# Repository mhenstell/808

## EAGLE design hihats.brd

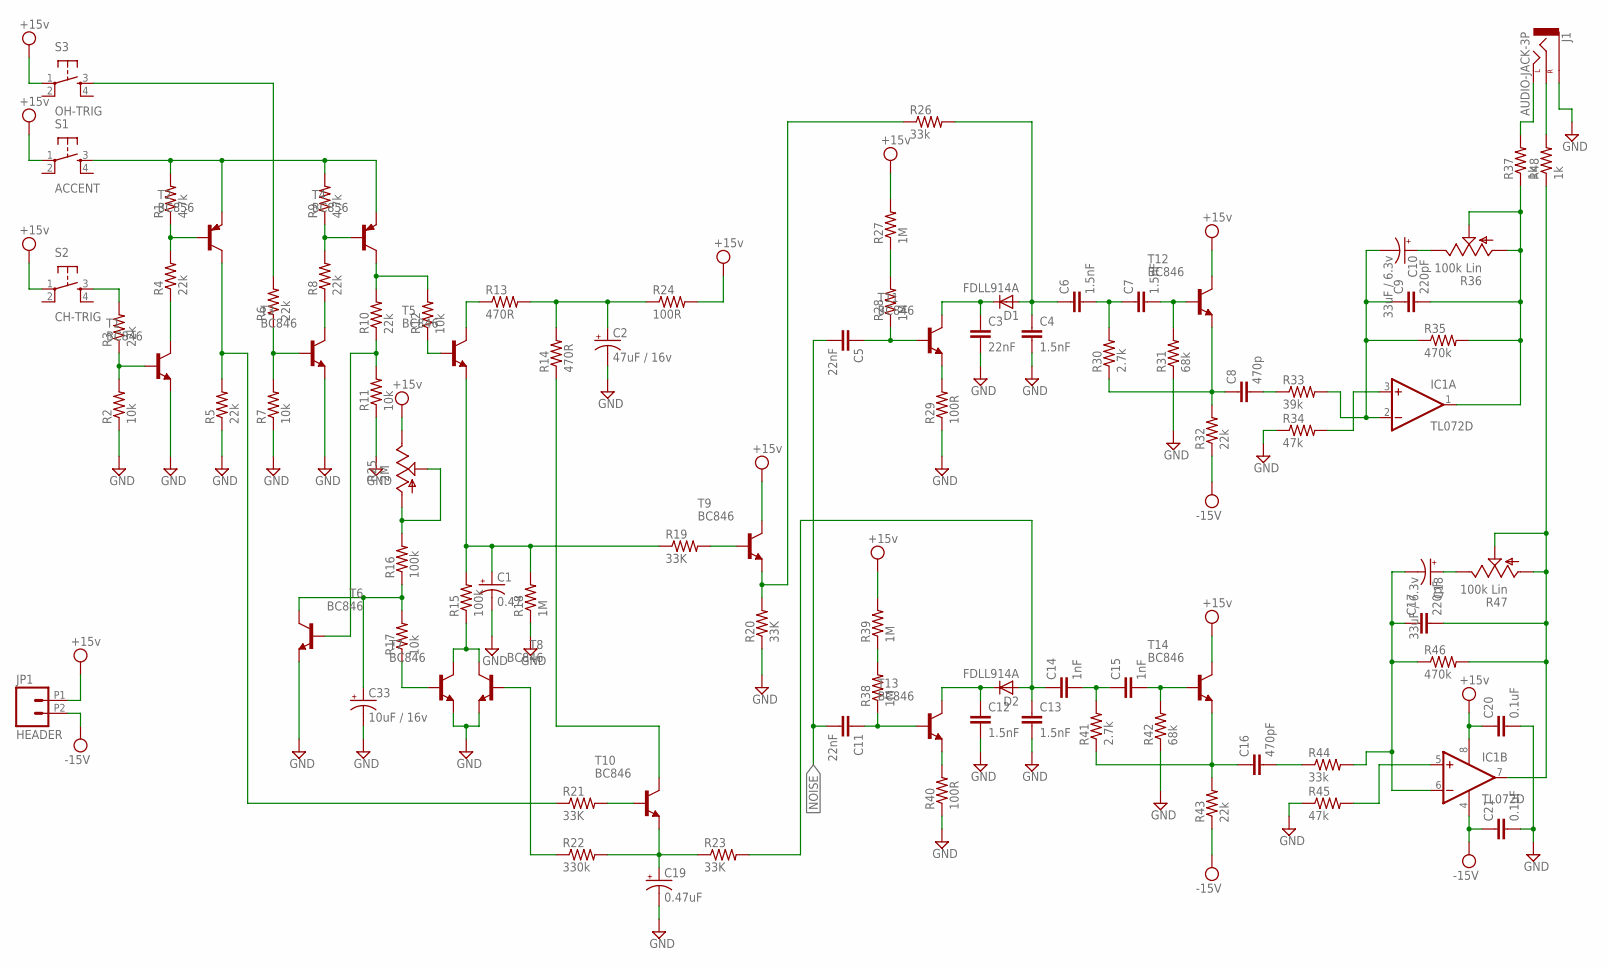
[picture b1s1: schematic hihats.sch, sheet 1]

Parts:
C1: 0.47; PANASONIC_VS_B-2; PARTNO EEE-1HAR47AR
C2: 47uF / 16v; PANASONIC_VS_B-2; PARTNO EEE-1CA470WR
C3, C5, C11: 22nF; 0805; PARTNO C0805C682K5RACTU
C4, C6, C7, C12, C13: 1.5nF; 0805; PARTNO C0805C682K5RACTU
C8: 470p; 0805; PARTNO C0805C682K5RACTU
C9, C17: 220pF; 0805; PARTNO C0805C682K5RACTU
C10, C18: 33uF / 6.3v; PANASONIC_VS_B-2; PARTNO EEE-1AA330WAR
C14, C15: 1nF; 0805; PARTNO C0805C682K5RACTU
C16: 470pF; 0805; PARTNO C0805C682K5RACTU
C19: 0.47uF; PANASONIC_VS_B-2; PARTNO UWJ1HR47MCL1GB
C20, C21: 0.1uF; 0805; PARTNO C0805C682K5RACTU
C33: 10uF / 16v; PANASONIC_VS_B-2; PARTNO EEE-1VA100WAR
D1, D2: FDLL914A; MELF-MLL34; PARTNO FDLL914A
IC1: TL072D; SO08; PARTNO TL072SG-13
J1: AUDIO-JACK-3P; CUI-352X-SMT; PARTNO SJ-3523-SMT-TR
JP1: HEADER; 1X02-5.08-SCREWTERM
R1, R9: 4.7k; 0805; PARTNO RMCF0805FT10K0
R2, R7, R11, R12, R17: 10k; 0805; PARTNO RMCF0805FT10K0
R3, R4, R5, R6, R8, R10, R32, R43: 22k; 0805; PARTNO RMCF0805FT10K0
R13, R14: 470R; 0805; PARTNO RMCF0805FT10K0
R15, R16: 100k; 0805; PARTNO RMCF0805FT10K0
R18, R27, R28, R38, R39: 1M; 0805; PARTNO RMCF0805FT10K0
R19, R20, R21, R23: 33K; 0805; PARTNO RMCF0805FT10K0
R22: 330k; 0805; PARTNO RMCF0805FT10K0
R24, R29, R40: 100R; 0805; PARTNO RMCF0805FT10K0
R25: 2M; POTENTIOMETER-3352P; PARTNO 3352P-1-205LF
R26, R44: 33k; 0805; PARTNO RMCF0805FT10K0
R30, R41: 2.7k; 0805; PARTNO RMCF0805FT10K0
R31, R42: 68k; 0805; PARTNO RMCF0805FT10K0
R33: 39k; 0805; PARTNO RMCF0805FT10K0
R34, R45: 47k; 0805; PARTNO RMCF0805FT10K0
R35, R46: 470k; 0805; PARTNO RMCF0805FT10K0
R36, R47: 100k Lin; POTENTIOMETER-CTS296; PARTNO 296UD104B1N
R37, R48: 1k; 0805; PARTNO RMCF0805FT10K0
S1: ACCENT; TACTILE_SWITCH_SMD; PARTNO PTS525SM10SMTR LFS
S2: CH-TRIG; TACTILE_SWITCH_SMD; PARTNO PTS525SM10SMTR LFS
S3: OH-TRIG; TACTILE_SWITCH_SMD; PARTNO PTS525SM10SMTR LFS
T1, T3, T5, T6, T7, T8, T9, T10, T11, T12, T13, T14: BC846; SOT23; PARTNO BC846BMTF
T2, T4: BC856; SOT23-BEC; PARTNO BC856BMTF

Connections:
+15V: C20.1, IC1.8 (V+), JP1.P1 (2), R24.2, R25.P$3 (E), R27.2, R39.2, S1.1, S2.1, S3.1, T9.3 (C), T12.3 (C), T14.3 (C); also elsewhere on the board
-15V: C21.1, IC1.4 (V-), JP1.P2 (1), R32.1, R43.1; also elsewhere on the board
GND: C1.-, C2.-, C3.2, C4.2, C12.2, C13.2, C19.-, C20.2, C21.2, C33.-, J1.1 (SLEEVE), R2.1, R5.1, R7.1, R11.1, R18.1, R20.1, R29.1, R31.1, R34.1, R40.1, R42.1, R45.1, T1.2 (E), T3.2 (E), T6.2 (E), T7.2 (E), T8.2 (E); also elsewhere on the board
unnamed: R1.2, R9.2, S1.3, T2.E, T4.E
unnamed: R1.1, R4.2, T2.B
unnamed: R3.2, S2.3
unnamed: R2.2, R3.1, T1.1 (B)
unnamed: R4.1, T1.3 (C)
unnamed: R8.2, R9.1, T4.B
unnamed: R5.2, R21.1, T2.C
unnamed: R6.2, S3.3
unnamed: R6.1, R7.2, T3.1 (B)
unnamed: R8.1, T3.3 (C)
unnamed: R10.2, R12.2, T4.C
unnamed: R10.1, R11.2, T6.1 (B)
unnamed: R12.1, T5.1 (B)
unnamed: R13.1, T5.3 (C)
unnamed: C2.+, R13.2, R14.2, R24.1
unnamed: R15.1, T7.3 (C), T8.3 (C)
unnamed: C33.+, R16.1, R17.2, T6.3 (C)
unnamed: R19.2, T9.1 (B)
unnamed: R17.1, T7.1 (B)
unnamed: R20.2, R26.1, T9.2 (E)
unnamed: R21.2, T10.1 (B)
unnamed: C1.+, R15.2, R18.2, R19.1, T5.2 (E)
unnamed: R22.1, T8.1 (B)
unnamed: C19.+, R22.2, R23.1, T10.2 (E)
unnamed: R14.1, T10.3 (C)
unnamed: C4.1, C6.1, D1.2 (A), R26.2
unnamed: R16.2, R25.P$1 (A), R25.P$2 (S)
unnamed: R27.1, R28.2
unnamed: C5.1, R28.1, T11.1 (B)
unnamed: R29.2, T11.2 (E)
unnamed: C3.1, D1.1 (C), T11.3 (C)
unnamed: C6.2, C7.1, R30.2
unnamed: C7.2, R31.2, T12.1 (B)
unnamed: C8.1, R30.1, R32.2, T12.2 (E)
unnamed: C8.2, R33.1
unnamed: C9.1, C10.-, IC1.2 (-IN), R33.2, R35.1
unnamed: IC1.3 (+IN), R34.2
unnamed: C9.2, IC1.1 (OUT), R35.2, R36.P$1 (A), R36.P$2 (S), R37.1
unnamed: R40.2, T13.2 (E)
unnamed: C10.+, R36.P$3 (E)
unnamed: C12.1, D2.1 (C), T13.3 (C)
unnamed: R38.2, R39.1
unnamed: C11.1, R38.1, T13.1 (B)
unnamed: C13.1, C14.1, D2.2 (A), R23.2
unnamed: C14.2, C15.1, R41.2
unnamed: C15.2, R42.2, T14.1 (B)
unnamed: C16.1, R41.1, R43.2, T14.2 (E)
unnamed: C16.2, R44.1
unnamed: C17.1, C18.-, IC1.6 (-IN), R44.2, R46.1
unnamed: IC1.5 (+IN), R45.2
unnamed: J1.2 (LEFT), R37.2
unnamed: C17.2, IC1.7 (OUT), R46.2, R47.P$1 (A), R47.P$2 (S), R48.1
unnamed: C18.+, R47.P$3 (E)
unnamed: J1.3 (RIGHT), R48.2
NOISE: C5.2, C11.2; also elsewhere on the board

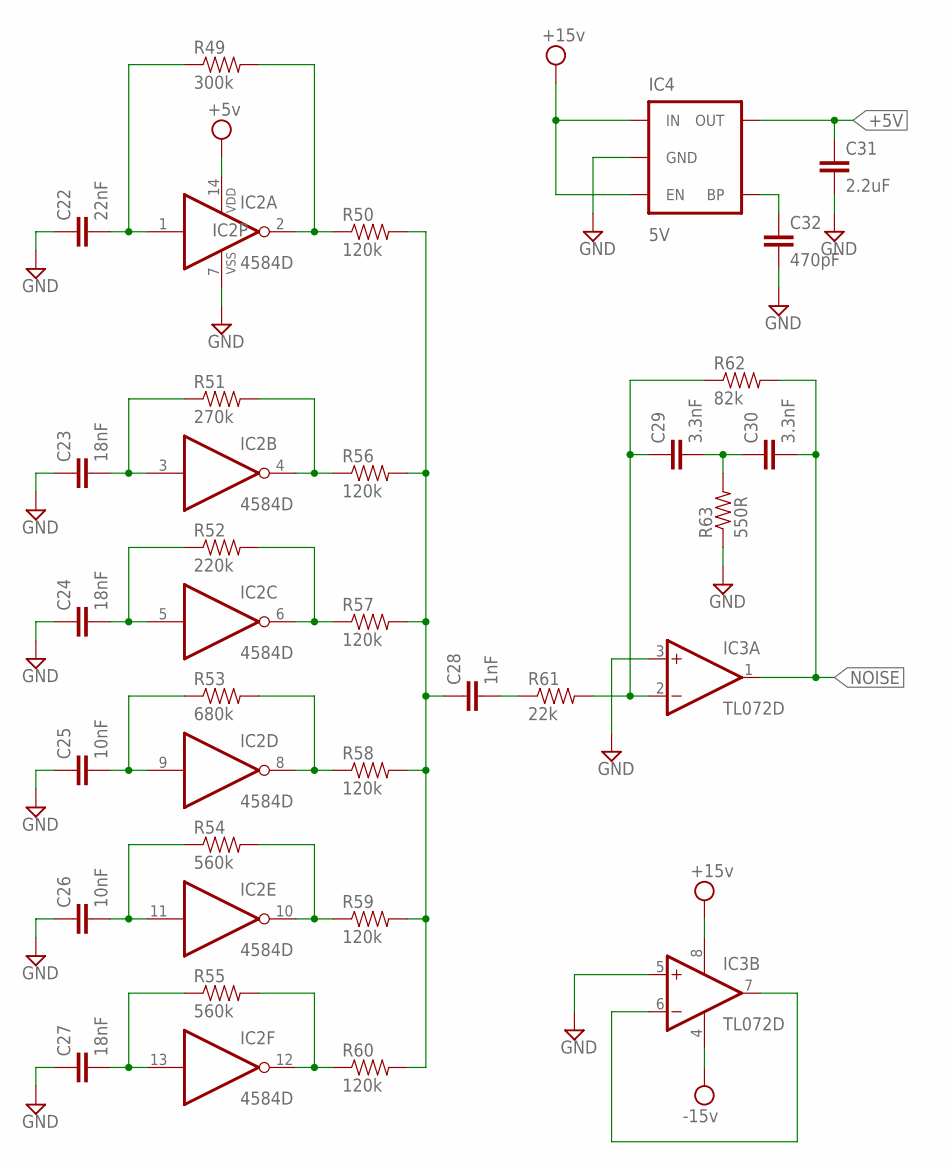
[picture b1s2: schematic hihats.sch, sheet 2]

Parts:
C22: 22nF; 0805; PARTNO C0805C682K5RACTU
C23, C24, C27: 18nF; 0805; PARTNO C0805C682K5RACTU
C25, C26: 10nF; 0805; PARTNO C0805C682K5RACTU
C28: 1nF; 0805; PARTNO C0805C682K5RACTU
C29, C30: 3.3nF; 0805; PARTNO C0805C682K5RACTU
C31: 2.2uF; 0805; PARTNO C0805C682K5RACTU
C32: 470pF; 0805; PARTNO C0805C682K5RACTU
IC2: 4584D; SO14; PARTNO BU4584BF-E2
IC3: TL072D; SO08; PARTNO TL072SG-13
IC4: 5V; SOT23-5; PARTNO MIC5205-5.0YM5 TR
R49: 300k; 0805; PARTNO RMCF0805FT10K0
R50, R56, R57, R58, R59, R60: 120k; 0805; PARTNO RMCF0805FT10K0
R51: 270k; 0805; PARTNO RMCF0805FT10K0
R52: 220k; 0805; PARTNO RMCF0805FT10K0
R53: 680k; 0805; PARTNO RMCF0805FT10K0
R54, R55: 560k; 0805; PARTNO RMCF0805FT10K0
R61: 22k; 0805; PARTNO RMCF0805FT10K0
R62: 82k; 0805; PARTNO RMCF0805FT10K0
R63: 550R; 0805; PARTNO RMCF0805FT10K0

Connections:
+5V: C31.1, IC2.14 (VDD), IC4.5 (OUT)
+15V: IC3.8 (V+), IC4.1 (IN), IC4.3 (EN); also elsewhere on the board
-15V: IC3.4 (V-); also elsewhere on the board
GND: C22.1, C23.1, C24.1, C25.1, C26.1, C27.1, C31.2, C32.2, IC2.7 (VSS), IC3.3 (+IN), IC3.5 (+IN), IC4.2 (GND), R63.1; also elsewhere on the board
unnamed: IC2.2 (O), R49.2, R50.1
unnamed: C22.2, IC2.1 (I), R49.1
unnamed: C27.2, IC2.13 (I), R55.1
unnamed: C26.2, IC2.11 (I), R54.1
unnamed: C25.2, IC2.9 (I), R53.1
unnamed: C24.2, IC2.5 (I), R52.1
unnamed: C23.2, IC2.3 (I), R51.1
unnamed: IC2.4 (O), R51.2, R56.1
unnamed: IC2.6 (O), R52.2, R57.1
unnamed: IC2.8 (O), R53.2, R58.1
unnamed: IC2.10 (O), R54.2, R59.1
unnamed: IC2.12 (O), R55.2, R60.1
unnamed: C28.1, R50.2, R56.2, R57.2, R58.2, R59.2, R60.2
unnamed: IC3.6 (-IN), IC3.7 (OUT)
unnamed: C28.2, R61.1
unnamed: C29.1, IC3.2 (-IN), R61.2, R62.1
unnamed: C29.2, C30.1, R63.2
unnamed: C32.1, IC4.4 (BP)
NOISE: C30.2, IC3.1 (OUT), R62.2; also elsewhere on the board

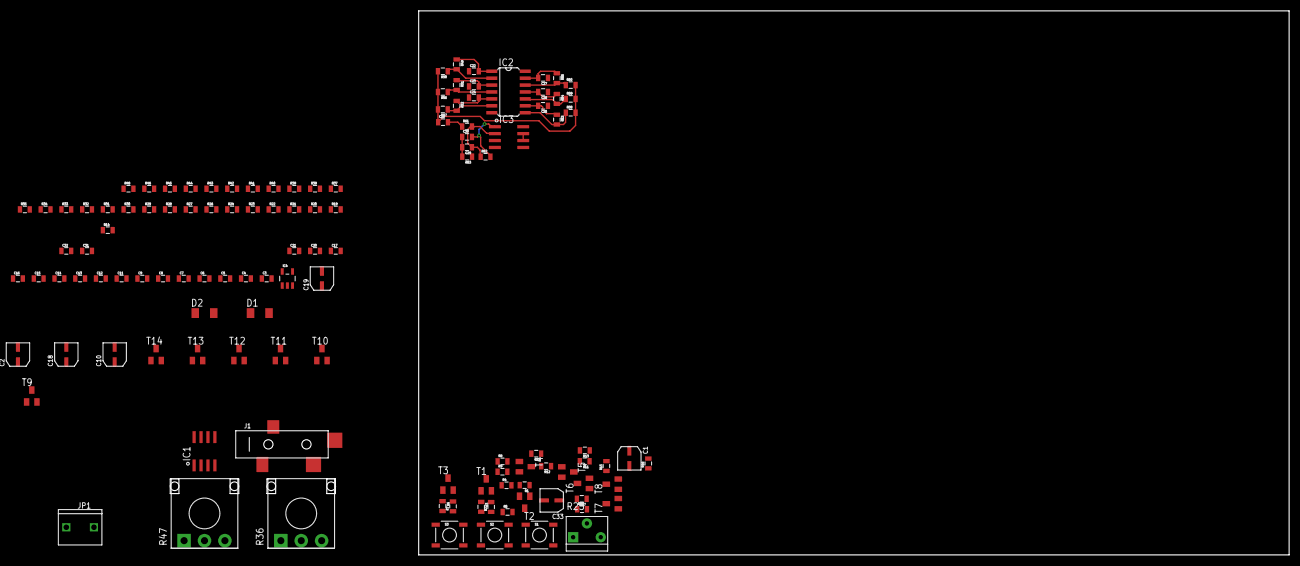
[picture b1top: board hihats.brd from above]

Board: 2 copper layers, 205.7 x 100.0 mm, 121 parts (0 on the bottom side), 77 nets.

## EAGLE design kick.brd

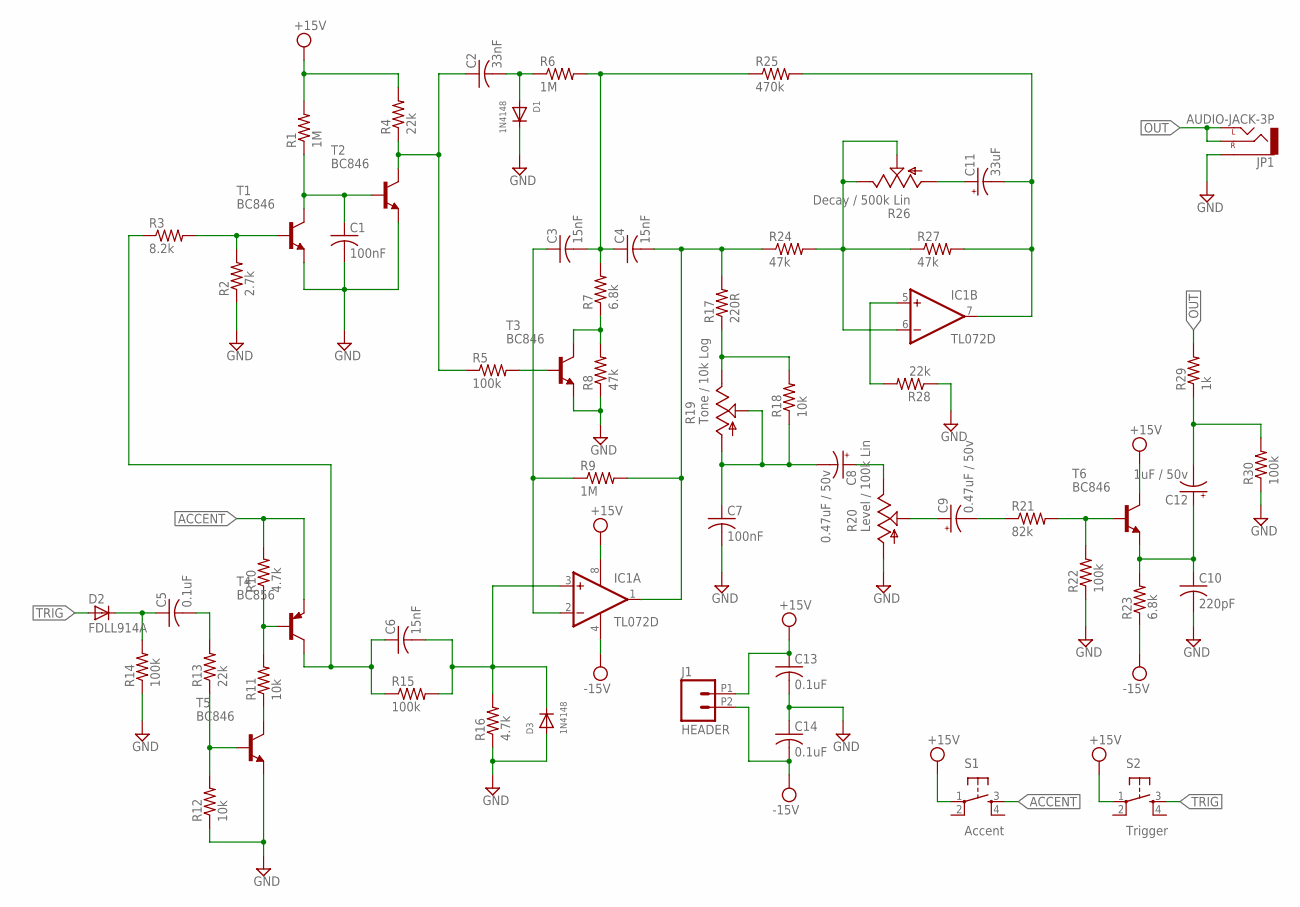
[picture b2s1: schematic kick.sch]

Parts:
C1, C7: 100nF; C0805; PARTNO C0805C104K5RACTU
C2: 33nF; C0805; PARTNO CL21B333KBANNNC
C3, C4, C6: 15nF; C0805; PARTNO CC0805KRX7R9BB153
C5, C13, C14: 0.1uF; C0805; PARTNO C0805C104K5RACTU
C8, C9: 0.47uF / 50v; PANASONIC_VS_B-2; PARTNO EEE-1HAR47AR
C10: 220pF; C0805; PARTNO CC0805KRX7R9BB221
C11: 33uF; PANASONIC_VS_B-2; PARTNO EEE-1AA330WAR
C12: 1uF / 50v; PANASONIC_VS_B-2; PARTNO EEE-1HA010SR
D1, D3: 1N4148; SOD-323F; PARTNO 1N4148WS
D2: FDLL914A; MELF-MLL34; PARTNO FDLL914A
IC1: TL072D; SO08; PARTNO TL072SG-13
J1: HEADER; 1X02-5.08-SCREWTERM
JP1: AUDIO-JACK-3P; CUI-352X-SMT; PARTNO SJ-3523-SMT-TR
R1, R6, R9: 1M; R0805; PARTNO RMCF0805FT1M00
R2: 2.7k; R0805; PARTNO RMCF0805FT2K70
R3: 8.2k; R0805; PARTNO RMCF0805FT8K20
R4, R13, R28: 22k; R0805; PARTNO RMCF0805FT22K0
R5, R14, R15, R22, R30: 100k; R0805; PARTNO RMCF0805FT100K
R7, R23: 6.8k; R0805; PARTNO MCR10ERTF6801
R8, R24, R27: 47k; R0805; PARTNO RMCF0805FT47K0
R10, R16: 4.7k; R0805; PARTNO RMCF0805FT4K70
R11, R12, R18: 10k; R0805; PARTNO RMCF0805FT10K0
R17: 220R; R0805; PARTNO RMCF0805FT220R
R19: Tone / 10k Log; POTENTIOMETER-PTV09; PARTNO PTV09A-4020F-A103
R20: Level / 100k Lin; POTENTIOMETER-CTS296; PARTNO 296UD104B1N
R21: 82k; R0805; PARTNO RMCF0805FT82K0
R25: 470k; R0805; PARTNO CRCW0805470KFKEA
R26: Decay / 500k Lin; POTENTIOMETER-PTV09; PARTNO 296UD504B1N
R29: 1k; R0805; PARTNO RMCF0805FT1K00
S1: Accent; TACTILE-SWITCH-SMD; PARTNO PTS525SM10SMTR LFS
S2: Trigger; TACTILE-SWITCH-SMD; PARTNO PTS525SM10SMTR LFS
T1, T2, T3, T5, T6: BC846; SOT23; PARTNO BC846BMTF
T4: BC856; SOT23-BEC; PARTNO BC856BMTF

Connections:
+15V: C13.1, IC1.8 (V+), J1.P1 (2), R1.2, R4.2, S1.1, S2.1, T6.3 (C)
-15V: C14.2, IC1.4 (V-), J1.P2 (1), R23.1
ACCENT: R10.2, S1.3, T4.E
GND: C1.2, C7.2, C10.2, C13.2, C14.1, D1.C, D3.A, JP1.1 (SLEEVE), R2.1, R8.1, R12.1, R14.1, R16.1, R20.P$1 (A), R22.1, R28.1, R30.1, T1.2 (E), T2.2 (E), T3.2 (E), T5.2 (E)
unnamed: C1.1, R1.1, T1.3 (C), T2.1 (B)
unnamed: C3.1, IC1.2 (-IN), R9.1
unnamed: C2.1, R4.1, R5.1, T2.3 (C)
unnamed: R2.2, R3.2, T1.1 (B)
unnamed: C2.2, D1.A, R6.1
unnamed: R5.2, T3.1 (B)
unnamed: R7.1, R8.2, T3.3 (C)
unnamed: C4.2, IC1.1 (OUT), R9.2, R17.2, R24.1
unnamed: C3.2, C4.1, R6.2, R7.2, R25.1
unnamed: C6.1, R3.1, R15.1, T4.C
unnamed: R11.1, T5.3 (C)
unnamed: R10.1, R11.2, T4.B
unnamed: R12.2, R13.1, T5.1 (B)
unnamed: C5.2, R13.2
unnamed: C5.1, D2.1 (C), R14.2
unnamed: C6.2, D3.C, IC1.3 (+IN), R15.2, R16.2
unnamed: R17.1, R18.2, R19.P$3 (E)
unnamed: C7.1, C8.-, R18.1, R19.P$1 (A), R19.P$2 (S)
unnamed: IC1.6 (-IN), R24.2, R26.P$2 (S), R26.P$3 (E), R27.1
unnamed: C8.+, R20.P$3 (E)
unnamed: C9.+, R20.P$2 (S)
unnamed: C9.-, R21.1
unnamed: R21.2, R22.2, T6.1 (B)
unnamed: C10.1, C12.+, R23.2, T6.2 (E)
unnamed: IC1.5 (+IN), R28.2
unnamed: C11.-, IC1.7 (OUT), R25.2, R27.2
unnamed: C11.+, R26.P$1 (A)
unnamed: C12.-, R29.1, R30.2
OUT: JP1.2 (LEFT), JP1.3 (RIGHT), R29.2
TRIG: D2.2 (A), S2.3

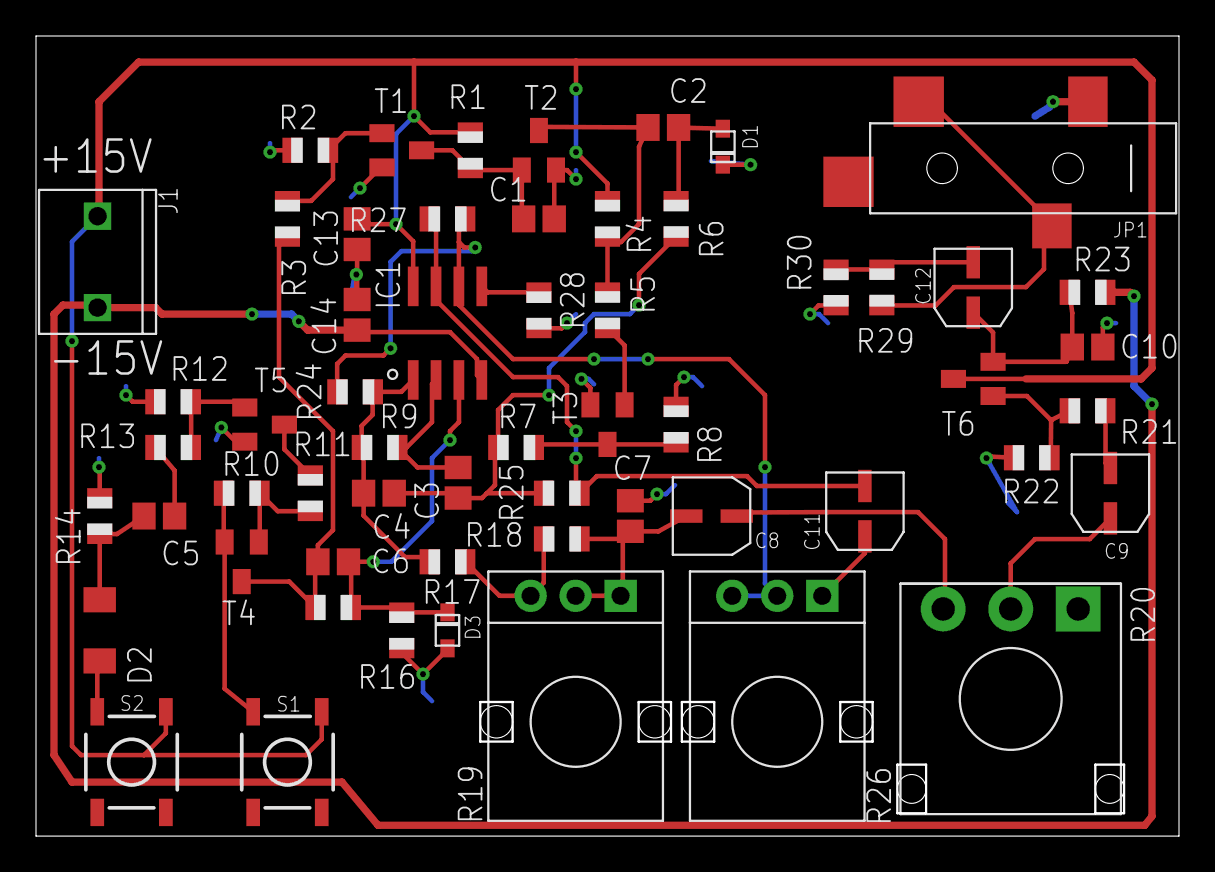
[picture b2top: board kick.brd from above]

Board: 2 copper layers, 63.5 x 44.5 mm, 58 parts (0 on the bottom side), 34 nets.

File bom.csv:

"Qty","Value","Part Num","Package","Parts","Mfg Name","VID","Vendor Part Num","Description","Pkg Code","XREF"
"3","0.1uF","C0805C104K5RACTU","C0805","C5, C13, C14","Kemet","DK","399-1170-1-ND","CAP CER 0.1UF 100NF 50V 10% X7R 0805","0805","REF10"
"2","0.47uF / 50v","EEE-1HAR47AR","PANASONIC_VS_B-2","C8, C9","Panasonic Electronic Components","DK","PCE4628CT-ND","CAP ALUM 0.47UF 50V 20%","PAN_VS_B","REF7"
"3","1M","RC2012F105CS","R0805","R1, R6, R9","Samsung Electro-Mechanics America Inc","DK","1276-5440-1-ND","RES 1M OHM 1/8W 1% 0805","0805 (2012 Metric)","REF12"
"2","1N4148","1N4148WS","SOD-323F","D1, D3","Fairchild Semiconductor","DK","1N4148WSFSCT-ND","DIODE SML SIG 75V 0.15A","SOD323F","REF2"
"1","1k","RC2012J102CS","R0805","R29","Samsung Electro-Mechanics America Inc","DK","1276-5531-1-ND","RES 1K OHM 1/8W 5% 0805","0805 (2012 Metric)","REF15"
"1","1uF / 50v","EEE-1HA010SR","PANASONIC_VS_B-2","C12","Panasonic Electronic Components","DK","PCE3912CT-ND","CAP ALUM 1.0UF 50V 20% SMD","PAN_VS_B","REF9"
"1","2.7k","RMCF0805JT2K70","R0805","R2","Stackpole Electronics Inc","DK","RMCF0805JT2K70CT-ND","RES 2.7K OHM 1/8W 5%","0805","REF21"
"2","4.7k","RMCF0805JT4K70","R0805","R10, R16","Stackpole Electronics Inc","DK","RMCF0805JT4K70CT-ND","RES 4.7K OHM 1/8W 5%","0805","REF26"
"2","6.8k","MCR10ERTF6801","R0805","R7, R23","Rohm Semiconductor","DK","RHM6.80KCHCT-ND","RES 6.8K OHM 1/8W 1% 0805","SMD","REF24"
"1","8.2k","RMCF0805JT8K20","R0805","R3","Stackpole Electronics Inc","DK","RMCF0805JT8K20CT-ND","RES 8.2K OHM 1/8W 5%","0805","REF22"
"3","10k","RC2012J103CS","R0805","R11, R12, R18","Samsung Electro-Mechanics America Inc","DK","1276-5552-1-ND","RES 10K OHM 1/8W 5% 0805","0805","REF14"
"3","15nF","CC0805KRX7R9BB153","C0805","C3, C4, C6","Yageo","DK","311-1143-1-ND","CAP CER 0.015UF 15nF 50V 10% X7R","0805","REF18"
"3","22k","RMCF0805JT22K0","R0805","R4, R13, R28","Stackpole Electronics Inc","DK","RMCF0805JT22K0CT-ND","RES 22K OHM 1/8W 5%","0805","REF23"
"1","33nF","CL21B333KBANNNC","C0805","C2","Samsung Electro-Mechanics America Inc","DK","1276-1796-1-ND","CAP CER 0.033UF 33nF 50V 10% X7R","0805","REF17"
"1","33uF","EEE-1AA330WAR","PANASONIC_VS_B-2","C11","Panasonic Electronic Components","DK","PCE4572CT-ND","CAP ALUM 33UF 10V 20%","PAN_VS_B","REF8"
"3","47k","RMCF0805JT47K0","R0805","R8, R24, R27","Stackpole Electronics Inc","DK","RMCF0805JT47K0CT-ND","RES 47K OHM 1/8W 5%","0805","REF25"
"1","82k","RMCF0805JT82K0","R0805","R21","Stackpole Electronics Inc","DK","RMCF0805JT82K0CT-ND","RES 82K OHM 1/8W 5%","0805","REF28"
"5","100k","RC2012J104CS","R0805","R5, R14, R15, R22, R30","Samsung Electro-Mechanics America Inc","DK","1276-5576-1-ND","RES 100K OHM 1/8W 5%","0805","REF13"
"2","100nF","C0805C104K5RACTU","C0805","C1, C7","Kemet","DK","399-1170-1-ND","CAP CER 0.1UF 100NF 50V 10% X7R 0805","0805","REF10"
"1","220R","RMCF0805JT220R","R0805","R17","Stackpole Electronics Inc","DK","RMCF0805JT220RCT-ND","RES 220 OHM 1/8W 5%","0805","REF27"
"1","220pF","CC0805KRX7R9BB221","C0805","C10","Yageo","DK","311-1123-1-ND","CAP CER 220PF 50V 10% X7R","0805","REF20"
"1","470k","RMCF0805JT470K","R0805","R25","Stackpole Electronics Inc","DK","RMCF0805JT470KCT-ND","RES 470K OHM 1/8W 5%","0805","REF29"
"1","AUDIO-JACK-3P","SJ-3523-SMT-TR","CUI-352X-SMT","JP1","CUI Inc","DK","CP-3523SJCT-ND","CONN AUDIO JACK 3.5MM STEREO SMD","None","REF33"
"1","Accent","PTS525SM10SMTR LFS","TACTILE-SWITCH-SMD","S1","C&K; Components","DK","CKN9104CT-ND","SWITCH TACTILE SPST-NO 0.05A 12V","None","REF16"
"5","BC846","BC846BMTF","SOT23","T1, T2, T3, T5, T6","Fairchild Semiconductor","DK","BC846BMTFCT-ND","TRANSISTOR NPN 65V 0.1A","SOT23","REF1"
"1","BC856","BC856BMTF","SOT23-BEC","T4","Fairchild Semiconductor","DK","BC856BMTFCT-ND","TRANSISTOR PNP 65V 100MA","SOT-23","REF3"
"1","Decay / 500k Lin","296UD504B1N","POTENTIOMETER-PTV09","R26","CTS Electrocomponents","DK","CT2270-ND","POT 500K OHM 1/8W CARB VERTICAL","THT","REF30"
"1","FDLL914A","FDLL914A","MELF-MLL34","D2","Fairchild Semiconductor","DK","FDLL914ACT-ND","DIODE SMALL SIG 100V 0.2A","LL34","REF4"
"1","HEADER","*","1X02-5.08-SCREWTERM","J1","*","*","*","*","*","*"
"1","Level / 100k Lin","296UD104B1N","POTENTIOMETER-CTS296","R20","CTS Electrocomponents","DK","CT2268-ND","POT 100K OHM 1/8W CARB VERTICAL","THT","REF31"
"1","TL072D","TL072SG-13","SO08","IC1","Diodes Incorporated","DK","TL072SG-13DICT-ND","IC OPAMP JFET 3MHZ","8SOP","REF5"
"1","Tone / 10k Log","PTV09A-4020F-A103","POTENTIOMETER-PTV09","R19","Bourns Inc.","DK","PTV09A-4020F-A103-ND","POT 10K OHM 9MM SQ .05W CARB","THT","REF32"
"1","Trigger","PTS525SM10SMTR LFS","TACTILE-SWITCH-SMD","S2","C&K; Components","DK","CKN9104CT-ND","SWITCH TACTILE SPST-NO 0.05A 12V","None","REF16"

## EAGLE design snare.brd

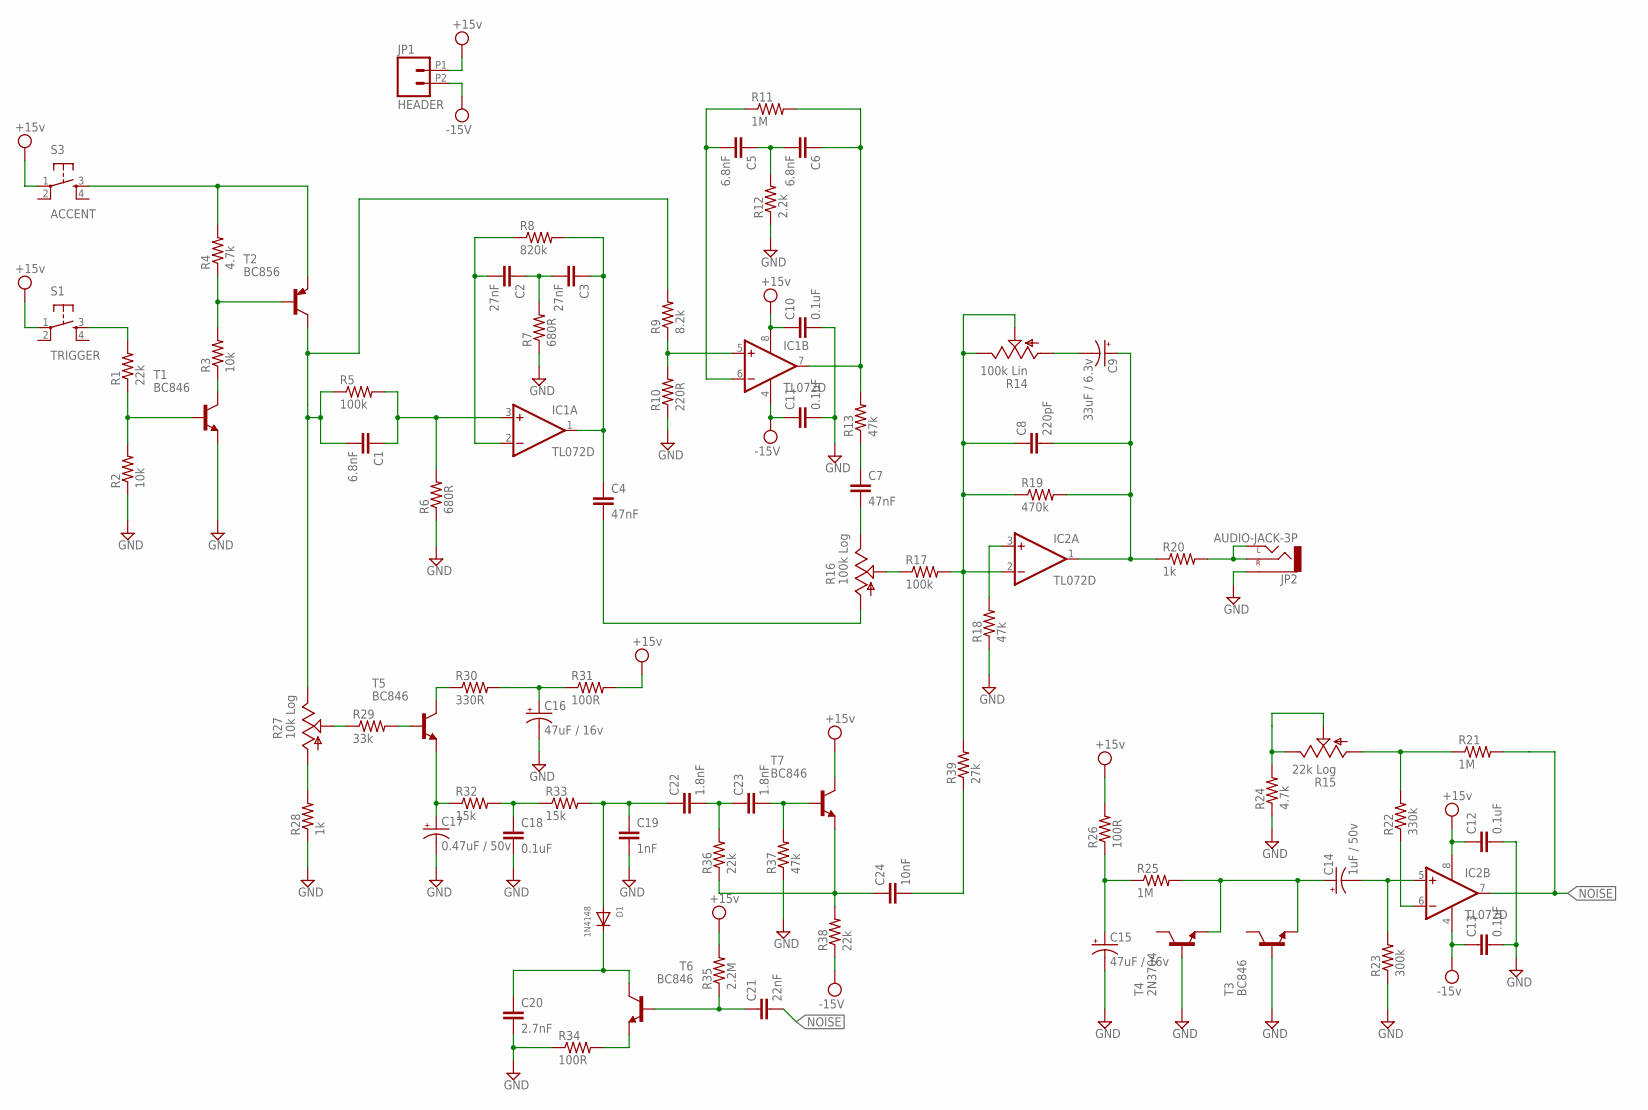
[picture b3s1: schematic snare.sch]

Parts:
C1, C5, C6: 6.8nF; 0805; PARTNO C0805C682K5RACTU
C2, C3: 27nF; 0805; PARTNO CC0805KRX7R9BB273
C4, C7: 47nF; 0805; PARTNO C0805C473K5RACTU
C8: 220pF; 0805; PARTNO CC0805KRX7R9BB221
C9: 33uF / 6.3v; PANASONIC_VS_B-2; PARTNO EEE-1AA330WAR
C10, C11, C12, C13, C18: 0.1uF; 0805; PARTNO C0805C104K5RACTU
C14: 1uF / 50v; PANASONIC_VS_B-2; PARTNO EEE-1HA010SR
C15, C16: 47uF / 16v; PANASONIC_VS_B-2; PARTNO EEE-1HAR47AR
C17: 0.47uF / 50v; PANASONIC_VS_B-2; PARTNO EEE-1HAR47AR
C19: 1nF; 0805; PARTNO C0805C102K5RACTU
C20: 2.7nF; 0805; PARTNO CC0805KRX7R9BB272
C21: 22nF; 0805; PARTNO CL21B223KBANNNC
C22, C23: 1.8nF; 0805; PARTNO 08055C182KAT2A
C24: 10nF; 0805; PARTNO GRM216R71H103KA01D
D1: 1N4148; SOD-323F; PARTNO 1N4148WS
IC1, IC2: TL072D; SO08; PARTNO TL072SG-13
JP1: HEADER; 1X02-5.08-SCREWTERM
JP2: AUDIO-JACK-3P; CUI-352X-SMT; PARTNO SJ-3523-SMT-TR
R1, R36, R38: 22k; 0805; PARTNO RMCF0805FT22K0
R2, R3: 10k; 0805; PARTNO RMCF0805FT10K0
R4, R24: 4.7k; 0805; PARTNO RMCF0805FT4K70
R5, R17: 100k; 0805; PARTNO RMCF0805FT100K
R6, R7: 680R; 0805; PARTNO RMCF0805FT680R
R8: 820k; 0805; PARTNO RC0805FR-07820KL
R9: 8.2k; 0805; PARTNO RMCF0805FT8K20
R10: 220R; 0805; PARTNO RMCF0805FT220R
R11, R21, R25: 1M; 0805; PARTNO RMCF0805FT1M00
R12: 2.2k; 0805; PARTNO RMCF0805FT2K20
R13, R18, R37: 47k; 0805; PARTNO RMCF0805FT47K0
R14: 100k Lin; POTENTIOMETER-CTS296; PARTNO 296UD104B1N
R15: 22k Log; POTENTIOMETER-PTV09-HORIZ; PARTNO PTV09A-4025F-A203
R16: 100k Log; POTENTIOMETER-PTV09-VERT; PARTNO PTV09A-2020F-A104
R19: 470k; 0805; PARTNO CRCW0805470KFKEA
R20, R28: 1k; 0805; PARTNO RMCF0805FT1K00
R22: 330k; 0805; PARTNO RMCF0805FT330K
R23: 300k; 0805; PARTNO RMCF0805FT300K
R26, R31, R34: 100R; 0805; PARTNO RMCF0805FT100R
R27: 10k Log; POTENTIOMETER-PTV09-HORIZ; PARTNO PTV09A-4020F-A103
R29: 33k; 0805; PARTNO RMCF0805FT33K0
R30: 330R; 0805; PARTNO RMCF0805FT330R
R32, R33: 15k; 0805; PARTNO RMCF0805FT15K0
R35: 2.2M; 0805; PARTNO RC0805FR-072M2L
R39: 27k; 0805; PARTNO RMCF0805FT27K0
S1: TRIGGER; TACTILE_SWITCH_SMD; PARTNO PTS525SM10SMTR LFS
S3: ACCENT; TACTILE_SWITCH_SMD; PARTNO PTS525SM10SMTR LFS
T1, T3, T5, T6, T7: BC846; SOT23; PARTNO BC846BMTF
T2: BC856; SOT23-BEC; PARTNO BC856BMTF
T4: 2N3704; TO92; PARTNO 2N3704

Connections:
+15V: C10.1, C12.1, IC1.8 (V+), IC2.8 (V+), JP1.P1 (2), R26.2, R31.2, R35.2, S1.1, S3.1, T7.3 (C)
-15V: C11.1, C13.1, IC1.4 (V-), IC2.4 (V-), JP1.P2 (1), R38.1
GND: C10.2, C11.2, C12.2, C13.2, C15.-, C16.-, C17.-, C18.2, C19.2, C20.2, JP2.1 (SLEEVE), R2.1, R6.1, R7.1, R10.1, R12.1, R18.1, R23.1, R24.1, R28.1, R34.1, R37.1, T1.2 (E), T3.1 (B), T4.1 (B)
unnamed: R1.2, S1.3
unnamed: R1.1, R2.2, T1.1 (B)
unnamed: R4.2, S3.3, T2.E
unnamed: R3.2, R4.1, T2.B
unnamed: R3.1, T1.3 (C)
unnamed: C1.2, R5.1, R9.2, R27.P$3 (E), T2.C
unnamed: C1.1, IC1.3 (+IN), R5.2, R6.2
unnamed: C2.2, IC1.2 (-IN), R8.1
unnamed: C2.1, C3.2, R7.2
unnamed: C3.1, C4.1, IC1.1 (OUT), R8.2
unnamed: IC1.5 (+IN), R9.1, R10.2
unnamed: C5.1, C6.2, R12.2
unnamed: C5.2, IC1.6 (-IN), R11.1
unnamed: C6.1, IC1.7 (OUT), R11.2, R13.2
unnamed: C7.2, R16.P$3 (E)
unnamed: C7.1, R13.1
unnamed: R16.P$2 (S), R17.1
unnamed: C4.2, R16.P$1 (A)
unnamed: C8.1, IC2.2 (-IN), R14.P$2 (S), R14.P$3 (E), R17.2, R19.1, R39.2
unnamed: IC2.3 (+IN), R18.2
unnamed: C8.2, C9.+, IC2.1 (OUT), R19.2, R20.1
unnamed: C9.-, R14.P$1 (A)
unnamed: R15.P$1 (A), R21.1, R22.2
unnamed: JP2.2 (LEFT), JP2.3 (RIGHT), R20.2
unnamed: IC2.6 (-IN), R22.1
unnamed: C14.-, IC2.5 (+IN), R23.2
unnamed: R15.P$2 (S), R15.P$3 (E), R24.2
unnamed: C14.+, R25.2, T3.2 (E), T4.3 (E)
unnamed: R27.P$1 (A), R28.2
unnamed: C15.+, R25.1, R26.1
unnamed: R27.P$2 (S), R29.1
unnamed: R29.2, T5.1 (B)
unnamed: R30.1, T5.3 (C)
unnamed: C16.+, R30.2, R31.1
unnamed: C17.+, R32.1, T5.2 (E)
unnamed: C18.1, R32.2, R33.1
unnamed: C19.1, C22.1, D1.A, R33.2
unnamed: C20.1, D1.C, T6.3 (C)
unnamed: R34.2, T6.2 (E)
unnamed: C21.1, R35.1, T6.1 (B)
unnamed: C22.2, C23.1, R36.2
unnamed: C23.2, R37.2, T7.1 (B)
unnamed: C24.1, R36.1, R38.2, T7.2 (E)
unnamed: C24.2, R39.1
NOISE: C21.2, IC2.7 (OUT), R21.2

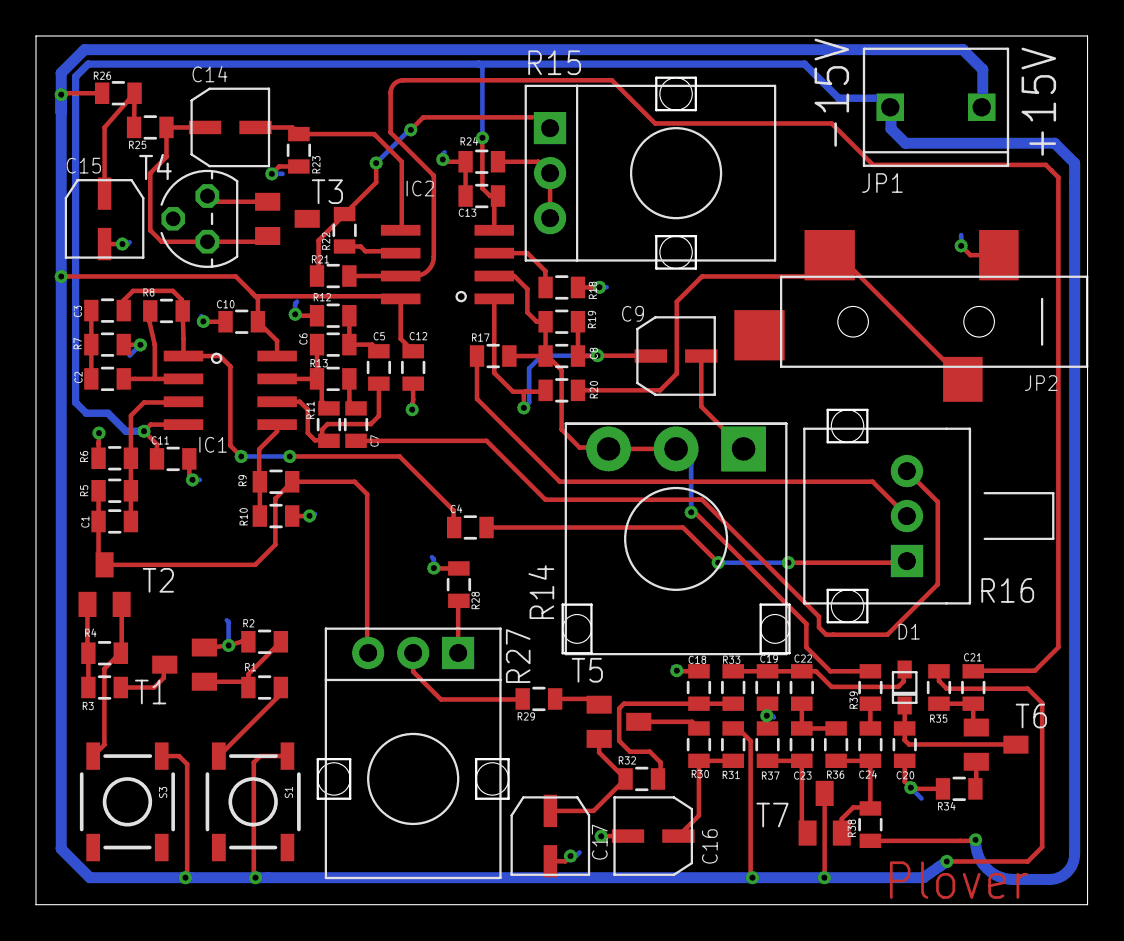
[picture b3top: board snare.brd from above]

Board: 2 copper layers, 58.4 x 48.3 mm, 77 parts (0 on the bottom side), 48 nets.

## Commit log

2014-06-18 init
2014-06-22 updating bom and pots
2014-06-22 regenerating brd
2014-06-22 layout
2014-06-23 v0.1
2014-06-23 renaming kick
2014-06-23 snare init
2014-06-24 snare layout
2014-06-24 added bom for snare
2014-06-24 fixed some part numbers
2014-06-25 hihats init
2014-06-30 fixed sch and started layout
2014-07-14 bom for hats, combined bom
2014-07-15 removing xls

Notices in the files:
parts and their libraries:
SparkFun-Electromechanical: Licensing: CC v3.0 Share-Alike You are welcome to use this library for commercial purposes.
SparkFun-PowerIC: Licensing: Creative Commons ShareAlike 4.0 International - https://creativecommons.org/licenses/by-sa/4.0
